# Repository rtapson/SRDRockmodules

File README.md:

# SRDRockmodules
A repository of information about SR&amp;D Rock Modules from the 1980's.

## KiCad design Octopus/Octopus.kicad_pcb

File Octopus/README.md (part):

# Octopus

A clone of the SR&D Octopus — a MIDI-controlled switcher — built around a **Teensy 4.1**. Unlike the audio-path loop switchers this generally gets compared to, this version drives **16 independent relay lines** on eight ¼" TRS jacks. Each jack's tip and ring are separate isolated contact closures to its sleeve, which is the standard dual-footswitch convention (e.g. channel on the tip, reverb on the ring). You patch them to amp channel/function jacks, other pedals' footswitch inputs, and so on. All 16 lines are recalled together as a single "preset" over MIDI, exactly like a footswitch controller flipping a bank on the original unit.

A separate **button panel** board (in `panel/`) puts 8 RGB-lit buttons on the front of the case, one per jack, to set and show each jack's lines by hand (see [Button panel](#button-panel)).

**Status:** firmware, and schematics plus fully routed 2-layer PCBs for both boards, are done. The hardware files are generated by scripts in `tools/` and verified with `kicad-cli` (ERC, DRC with schematic parity), full netlist checks, and rendered previews. Open `Octopus.kicad_pro` and `panel/OctopusPanel.kicad_pro` in KiCad to review. Both boards are fitted to the Rockmodule case model in `case/` (see [Fit in the case](#fit-in-the-case)). Nothing has been fabricated or bench-tested yet.

## Block diagram

```
MIDI IN (J1, FM6725) --220R--> 6N138 opto (isolated) --> Teensy 4.1 RX1 (3.3 V side)
                                                   \--> 74HCT14 x2 (5 V) --220R--> MIDI THRU (J12, FM6725)

                        +--------------------------+
                        |  Teensy 4.1              |
                        |  - MIDI parsing          |
                        |  - preset table (EEPROM) |
                        |  pins 2-9    pins 24-31  |
                        +--------------------------+
                               |            |
                               v            v
                        ULN2803A U3    ULN2803A U5      (sink the relay coils)
                               |            |
                               v            v
                     8x relay (tips)         8x relay (rings)
                               |            |
                  8x NO/NC jumper         8x NO/NC jumper
                               |            |
                               v            v
            8x Switchcraft RN112BPC 1/4" TRS jack: tip = line n, ring = line n+8, sleeve = common

9-12VDC in (J2 screw terminal) --> polyfuse --> Recom R-78E 5 V switcher --> +5V: Teensy VIN, relay coils, ULN COMs
Teensy 3.3 V pin --> +3V3: 6N138 output side + RX1 pull-up

Teensy I2C0 (pins 18/19) + pin 22 --J11, 6-pin cable--> button panel: 8x red/green button, PCA9685, MCP23017, OLED, encoder
```

## Bill of materials

`BOM_DigiKey.csv` lists every part for one unit (both boards and the panel cable) by manufacturer part number, ready to upload to DigiKey's BOM Manager. Mechanical hardware isn't in it: see the notes after the table below.

| Ref | Part | Footprint | Notes |
|---|---|---|---|
| U1 | PJRC Teensy 4.1 | `Octopus:Teensy41_Socketed` | Mounted on 2x24 female headers. Custom symbol/footprint in this folder (`Octopus.kicad_sym`, `Octopus.pretty`); only the pins this design uses are in the symbol |
| U2 | 6N138 | DIP-8 | MIDI IN opto-isolator; output side runs from the Teensy's 3.3 V |
| U3, U5 | ULN2803A | DIP-18 | Octal Darlington sink drivers (U3 = tip lines, U5 = ring lines), internal flyback diodes |
| U4 | Recom R-78E5.0-1.0 | SIP-3 (`RECOM_R-78E`) | 5 V / 1 A switching regulator, 7805 pinout. Runs cool at the ~630 mA load, where a 7805 would burn ~4.4 W from 12 V |
| C1 | 10 µF 25 V electrolytic | radial 6.3 mm | Regulator input capacitor |
| C2 | 22 µF 16 V electrolytic | radial 6.3 mm | Regulator output capacitor |
| K1-K16 | Omron G5V-1 (5 VDC coil) | `Relay_SPDT_Omron_G5V-1` | SPDT: COM = pins 5+6, NC = pin 1, NO = pin 10. K1-K8 switch jack tips, K9-K16 rings |
| D1 | 1N4148 | DO-35 | Reverse-parallel across the opto LED (MIDI reverse-voltage protection) |
| R1 | 220 Ω | axial 0207 | In series between DIN pin 4 and the opto LED (MIDI spec) |
| R2 | 470 Ω | axial 0207 | Opto output pull-up to **3.3 V** (Teensy 4.1 pins are not 5 V tolerant) |
| J1 | Cliff FM6725 (DIN-5 180°, screened, right-angle PCB) | `Octopus:DIN-5_180deg_Cliff_FM6725_Horizontal` | **MIDI IN**, through the back panel. Only pins 4 and 5 are used; pin 2 and the screen are left unconnected, as the MIDI spec requires for an input |
| J12 | Cliff FM6725 | `Octopus:DIN-5_180deg_Cliff_FM6725_Horizontal` | **MIDI THRU**, through the back panel. Pin 4 → 220 Ω → +5 V, pin 5 → 220 Ω → U6, pin 2 and the screen to GND |
| U6 | 74HCT14 | DIP-14 | MIDI THRU buffer: two inverters in series from the opto output. HCT's TTL input thresholds take the 3.3 V signal while it drives the 5 V MIDI loop. The other four gates' inputs are grounded |
| R3, R4 | 220 Ω | axial 0207 | MIDI THRU source resistors (pins 4 and 5) |
| C3 | 100 nF ceramic | disc, 5 mm pitch | U6 decoupling |
| J2 | 2-way 5.08 mm screw terminal (Phoenix MKDS 1,5/2-5.08) | TerminalBlock_Phoenix_MKDS-1,5-2-5.08 | 9-12 VDC in (1 = +, 2 = GND). The back panel has no DC jack hole, so this takes a pigtail through the cord hole now, and the DC output of a mains module later |
| J3-J10 | Switchcraft RN112BPC | `RN112BPC:SWITCHCRAFT_RN112BPC` (SnapMagic, in `case/RN112BPC`) | Outputs 1-8 (jack 1 is the leftmost seen from the back). ¼" 3-conductor right-angle Hi-D Jax, double open circuit, thermoplastic body, PC terminals. Tip = line n, ring = line n+8, sleeve = common for both |
| JP1-JP16 | 3-pad solder jumper (PCB copper, not a part) | `SolderJumper-3_P1.3mm_Bridged12` | Per-line NO/NC select, on the **bottom** side directly behind each relay, labelled NO / NC. Ships bridged to **NO**: the jack contact is shorted to sleeve while the line is on. For **NC** (open while the line is on), cut the thin trace between the "NO" pad and the center pad, then solder-bridge the center pad to the "NC" pad |
| F1 | Bourns MF-RHT070 (0.7 A hold) | radial | Input polyfuse |
| J11 | JST-XH 6-pin (B6B-XH-A) | JST_XH_B6B-XH-A | Cable to the button panel's J1, wired pin-for-pin: 1 +5V, 2 +3V3, 3 GND, 4 SDA, 5 SCL, 6 INT |
| H1, H2 | M3 mounting holes | 3.2 mm | On the case floor's two screw bosses; the jack nuts hold the back edge. Needs ~1.8-2 mm spacers (see below) |

## Pin map (Teensy 4.1)

| Teensy pin | Function |
|---|---|
| 0 (RX1) | MIDI IN (Serial1), from the opto output. The same node feeds the hardware MIDI THRU, so THRU works whatever the firmware is doing; the MIDI library's software thru is turned off |
| 2-9 | Lines 1-8 (jack 1-8 **tip**) via U3 |
| 24-31 | Lines 9-16 (jack 1-8 **ring**) via U5 |
| 18, 19 | I2C0 SDA / SCL to the button panel (pull-ups are on the panel) |
| 22 | Button panel interrupt (MCP23017 INTA, open-drain, Teensy internal pull-up) |
| VIN | +5 V from U4 |
| 3.3V | Powers the 6N138 output side and the RX1 pull-up |
| GND | Common ground |
| USB | Config/debug console (see `firmware/README.md`) |

The firmware's pin table (`firmware/src/RelayBank.cpp`) uses this same map. Pins 2-9 and 24-31 are the two runs of consecutive pins along one header row, so each driver sits directly under its group. Within each driver, slot *k* uses input I(9−k)/output O(9−k). That reversal only exists so the driver traces run straight, and it's invisible to the firmware.

## MIDI control spec

- **Program Change (0-127)** recalls stored preset 1-128 (PC 0 = preset 1, as shown on the display): all 16 lines are set at once from that preset's 16-bit pattern (bit N = line N+1, 1 = on).
- **Control Change 102-117** switches line 1-16 individually: value >= 64 = on, < 64 = off. These CCs are left undefined by the MIDI spec. The old 8-line range (20-27) couldn't simply be extended to 20-35, because CC 32 is Bank Select LSB.
- **MIDI channel**: omni by default; can be pinned to a single channel via the serial config console (see firmware README).
- Presets and channel persist across power cycles in the Teensy's emulated EEPROM.

## PCB

- One flat, 2-layer board, 205.8 × 111.7 mm, all through-hole except the 16 solder jumpers (bare copper on the bottom). GND pour on both layers.
- Layout, from the back edge forward: the eight RN112BPC jacks on a 17.78 mm (0.700") pitch, then the MIDI IN and THRU sockets and the power terminal J2 just inside the cord hole; for each jack, its tip relay and ring relay side by side; the two ULN2803As, each directly behind its Teensy pin group; the Teensy (USB toward the right side). The MIDI opto, THRU buffer and regulator are just in front of the DIN sockets. The button-panel header J11 is at the front edge.
- Net classes (in `Octopus.kicad_pro`): Default 0.3 mm, **Power** (+5V, GND, raw DC in) 0.8 mm, **Relay** (the `/CHn_*` and `/JACKn_SLV` contact nets) 0.6 mm, which is ample for the relays' 1 A rating. Relay clearance is 0.24 mm because the solder jumper's pads are 0.25 mm apart by design, which is fine for the low-voltage duty these relays are limited to anyway (see cautions). Freerouting routes with a 10 µm margin over every clearance, so its rounding can't land a track under KiCad's rule.
- Verified: `kicad-cli pcb drc --schematic-parity --refill-zones` → 0 errors, 0 unconnected, 0 parity issues; ERC 0 errors. The only DRC warnings are 16 × *silkscreen clipped by board edge*: SnapMagic's RN112BPC outline includes the bushing, which overhangs the back edge by design. The library footprint is used exactly as supplied, so these are left alone.
- Jack 8's tip run (from its tip pin, down the gap beside the rear-post notch, to JP8 under relay K8) is laid by hand and locked before autorouting (`add_preroutes()` in `gen_pcb.py`); Freerouting otherwise boxes that pin in.

### Fit in the case

Measured from `case/Bottom.step`, `Top.step` and `BackPanel.step` (the back panel's STEP sits 53.34 mm behind the case; it belongs in the back groove, inside face at y = 64.77 mm in the case frame). All in `tools/gen_pcb.py`, `case geometry` section.

- **Jacks.** The RN112BPC is a right-angle jack: it lies on the board, pins down, with its plug axis 9.65 mm (0.380") above the board surface. Its body's front face seats against the inside of the back panel and the 3/8-32 bushing passes through the Ø9.52 mm hole; the washer and nut go on the outside and hold the board's back edge. The symbol, footprint and 3D model are SnapMagic's (`case/RN112BPC`, wired in through the project's `sym-lib-table` and `fp-lib-table`). The footprint agrees with Switchcraft's customer drawing *RN111-RN114 SERIES, right angle Hi-D Jax* rev E: its origin is the sleeve pin, 5.68 mm behind the body's front face, and the tip pin is 12.70 mm further back. The locating-post holes are 2.69 mm, against the drawing's 2.41 mm. The schematic generator embeds the symbol after upgrading it with `kicad-cli sym upgrade` (it's in KiCad 6 format). `gen_pcb.py` attaches the STEP model when it places the jacks, turned 180° and shifted 12.7 mm to match the footprint. The model also contains the nut and washer, drawn floating in front of the bushing, and a flat 'confidential' label plate; both are cosmetic and only show in the 3D view.
- **Board height.** The jack holes are 18.10 mm above the case bottom, so the board's top must sit at **8.45 mm**, bottom at 6.85 mm. The floor bosses' tops are at 5.02 mm (right one 4.89 mm), so put **~1.8-2.0 mm spacers** (nylon washers, or 2 mm M3 spacers) between the bosses and the board. The panel holes are the same size as the bushings, so the jacks can't take up much error: check the height with the jacks' nuts loose before tightening.
- **DIN sockets.** The FM6725 is a right-angle socket with its front face on the inside of the panel, like the jacks, so its centre is 10.3 mm above the board: **18.75 mm** above the case bottom, 0.65 mm higher than the jacks. The footprint follows the Cliff datasheet (`case/screeneddins.pdf`) and was checked against `case/FM6725.stp`, which KiCad uses as the 3D model. That model puts the centre 0.2 mm lower, at 10.1 mm, which a Ø15 panel hole easily absorbs.
- **Outline.** It fills the case between the side walls (x ±102.9 mm), from 64.2 mm (0.57 mm short of the back panel; the bushings overhang the edge) to 47.5 mm forward of centre, which clears the parts on the back of the button board. The three screw posts that join the case halves (4.75 mm radius at board height) pass through a Ø10.5 mm hole at the front and two notches at the back corners. The jack bodies end about 2 mm in front of the rear posts. Jack 8's two relays sit further forward, below the notch, because the left rear post is where they would go.
- **Headroom.** The case roof is 32.6 mm above the board, which clears everything (the Teensy on headers is ~13 mm, the jacks 17 mm). Under the board, 4.6 mm clears the trimmed through-hole leads.
- **Future mains power.** The DIN sockets now fill the back corner, so the space kept free for a 12 V mains module is the **front right** of the board (~50 × 52 mm, marked on `Dwgs.User`), with the cord running forward to it from the hole. Its DC output goes to J2, so the regulator stays as it is.

### Back panel holes

The main board fixes where every hole in the back panel goes. Jack 8 sits 0.8 mm clear of the left groove rib, and from jack 1 on come MIDI IN, MIDI THRU and the cord hole, 1.5 mm apart. **These differ from the current `BackPanel.step`:** the jacks close up from a 0.75" to a 0.700" pitch, the two DIN holes are new, and the cord hole moves 3.67 mm toward the edge. Positions are measured on the panel **seen from behind the unit**, from its left and bottom edges (the panel is 211.18 × 38.61 mm). The last three columns are the same centres in the case frame of the STEP files (x across, z up), plus how far each hole moved.

| Hole | From left edge (mm) | From bottom edge (mm) | Diameter (mm) | Case x | Case z | Moved in x |
|---|---|---|---|---|---|---|
| Power cord | 13.79 | 19.31 | 14.48 | 91.68 | 21.53 | +3.67 |
| MIDI THRU | 33.03 | 16.53 | 15.0 | 72.44 | 18.75 | new |
| MIDI IN | 55.53 | 16.53 | 15.0 | 49.94 | 18.75 | new |
| Jack 1 | 75.47 | 15.88 | 9.52 | 30.00 | 18.10 | −10.34 |
| Jack 2 | 93.25 | 15.88 | 9.52 | 12.22 | 18.10 | −9.07 |
| Jack 3 | 111.03 | 15.88 | 9.52 | −5.56 | 18.10 | −7.80 |
| Jack 4 | 128.81 | 15.88 | 9.52 | −23.34 | 18.10 | −6.53 |
| Jack 5 | 146.59 | 15.88 | 9.52 | −41.12 | 18.10 | −5.26 |
| Jack 6 | 164.37 | 15.88 | 9.52 | −58.90 | 18.10 | −3.99 |
| Jack 7 | 182.15 | 15.88 | 9.52 | −76.68 | 18.10 | −2.72 |
| Jack 8 | 199.93 | 15.88 | 9.52 | −94.46 | 18.10 | −1.45 |

The DIN holes only need to pass the plug's shell into the socket (Ø14 opening), so Ø15.0 is a suggestion; check it against your cables. The 0.700" pitch leaves ~1.9 mm between the 15.88 mm jack bodies, and between the washers (0.625" max per Switchcraft).

### Cautions before ordering

1. **Power.** Worst-case 5 V load is about 800 mA: 16 coils × 30 mA, the Teensy, and all 8 buttons lit amber (≈26 mA each: 10 mA red + 16 mA green). That's within the R-78E5.0-1.0's 1 A. From 12 V it draws about 0.4 A at the input, comfortably under the polyfuse's 0.7 A hold. The panel's logic (~10 mA) runs from the Teensy's 3.3 V pin, which can supply 250 mA.
2. **Teensy VIN/VUSB.** If USB may be plugged in while J2 is powered, cut the VIN–VUSB trace on the Teensy's underside (per PJRC). Otherwise the two supplies back-feed each other.
3. **Contact ratings.** The G5V-1 is rated 1 A at 30 VDC (0.5 A at 125 VAC), and the board's clearances are sized for low voltage. **Don't switch mains** with this board as-is. Likewise, don't bring the mains cord onto this board: a mains module needs its own creepage-rated wiring and fusing.
4. **Shared sleeve.** A jack's tip and ring lines share its sleeve as their common, as dual footswitches expect. They are not isolated from each other the way separate jacks are.
5. **No status LEDs on the main board.** The front-panel buttons show every line. For bench testing without the button board, the serial console (`DUMP`) or a meter on the jacks will show what's switched.

## Button panel

A separate board (`panel/OctopusPanel.*`) slides into the groove in the case top and bottom, just behind the front panel, with 8 illuminated buttons (one per output jack), a 0.96" OLED showing the current preset, and a rotary encoder with push switch for picking presets.

| Button LED | Jack state |
|---|---|
| off | tip and ring both off |
| red | tip on |
| green | ring on |
| amber (red + green) | tip and ring both on |

- **Press** (acts on release) to step a jack: off → red → green → amber → off.
- **Hold 2 s** to save all 16 lines into the current preset (the one on the display). The LEDs blink off once, the display says SAVED, and the serial console prints the number.
- **Display:** the current preset, **1-128** (MIDI Program Change 0 = preset 1), in big digits. "EDITED" appears when the buttons have changed the lines since the preset was loaded (hold a button to save it, or recall the preset to drop the change).
- **Encoder:** turn to pick a preset. The display shows it under an inverted SELECT? label (turning wraps 128 → 1). **Push** to load it, which is the same as a MIDI Program Change. Leave it for 5 s and the display goes back to the current preset without changing anything.
- The LEDs always mirror the relays, so MIDI program changes and CCs show up on the buttons too.
- If the panel isn't connected, the main board runs normally without it.

**Circuit.** The switches are **Omron B3W-9000-RG2N**: 10 × 10 mm milky-white cap, with a red and a green LED on separate leads. Both anodes go to +5V, and each cathode has its own resistor: 330 Ω red (≈10 mA) and 180 Ω green (≈16 mA), in four isolated 4-resistor arrays (Bourns CAT16-331J4 / -181J4, 1206). RN1 and RN2 carry the red of buttons 1-4 and 5-8, RN3 and RN4 the green. Each element dissipates at most ~46 mW of its 62.5 mW rating. That's Omron's recommended 12:20 red:green ratio for an even amber, scaled down a little. The cathodes go to one **PCA9685** PWM LED driver (U1 @0x40: red LED0-7, green LED8-15). The chip runs at 3.3 V with open-drain outputs, which are 5.5 V tolerant, so the Teensy's I²C stays at 3.3 V (NXP datasheet, "direct LED connection"). The buttons and the encoder go to an **MCP23017** (U3 @0x20: buttons 1-7 on GPA0-6, button 8 on GPB0, encoder A/B/push on GPB1-3), with its interrupt (INTA, mirrored for both ports) on Teensy pin 22. GPA7 and GPB7 are left unused: Microchip's current datasheet makes them output-only. Each encoder line has a 10 kΩ pull-up and 10 nF to ground. The display is a **Winstar WEA012864D-03** 0.96" 128×64 SSD1306 module at I²C 0x3C, powered from 3.3 V (12 mA typical). Generic 0.96" modules usually share its outline, but check the pin order: many swap VCC and GND, and this board expects VCC, GND, SCL, SDA from the left, seen from the front. The only I²C pull-ups (4.7 kΩ) are on the panel. Red and green brightness (and so the amber mix) can be trimmed in firmware (`kLevelRed/Green` in `Panel.h`).

*Why not RGB?* The first choice, CTS 228CMVARGBFR, is discontinued, and no stocked RGB tactile switch was tall enough to reach through the panel. The only RGB one found, E-Switch TL3220, is 2 mm tall and would need custom light-pipe caps. With two LEDs, "both lines on" shows as amber, the mix of the other two colours.

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
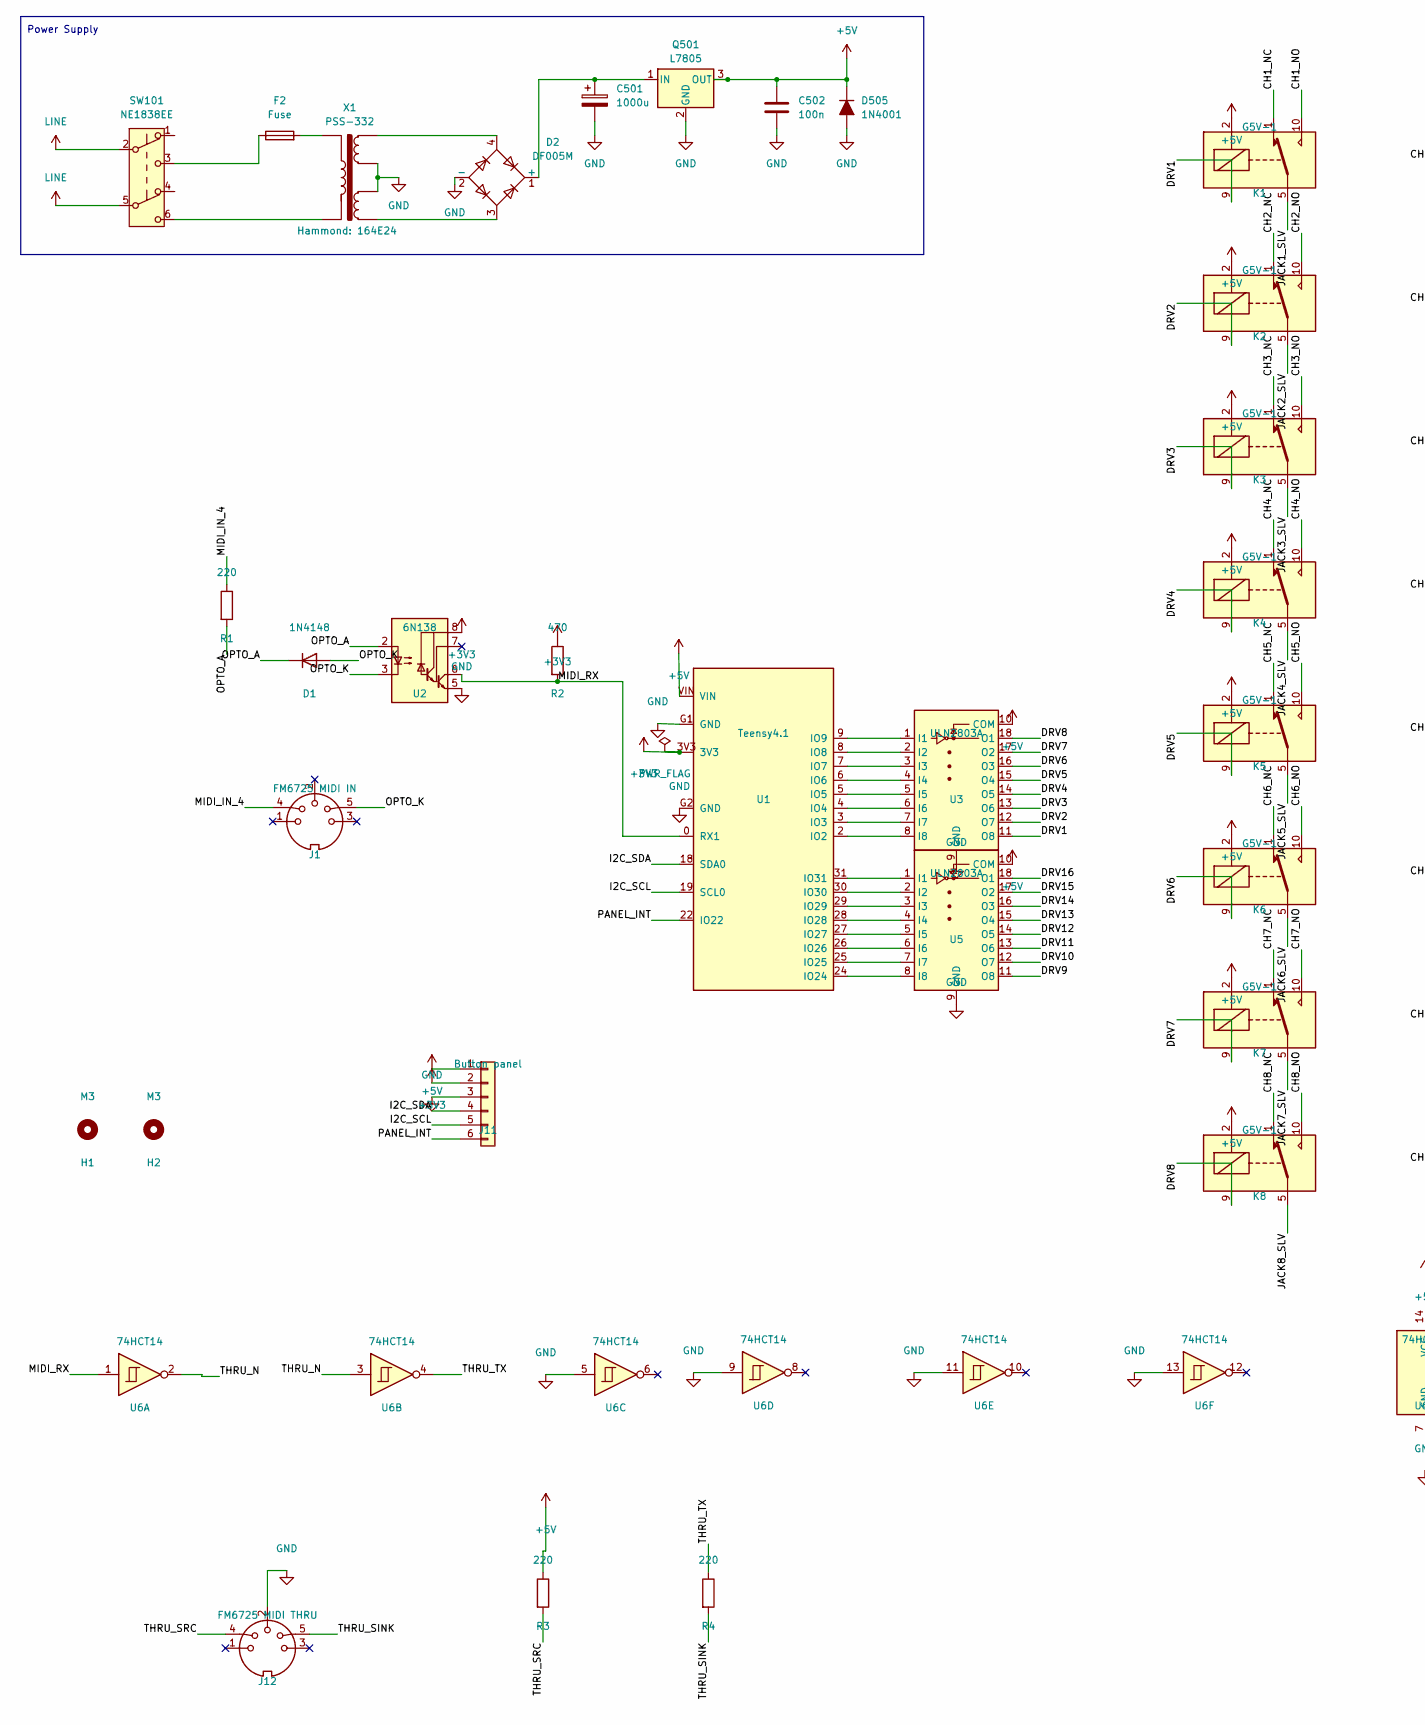
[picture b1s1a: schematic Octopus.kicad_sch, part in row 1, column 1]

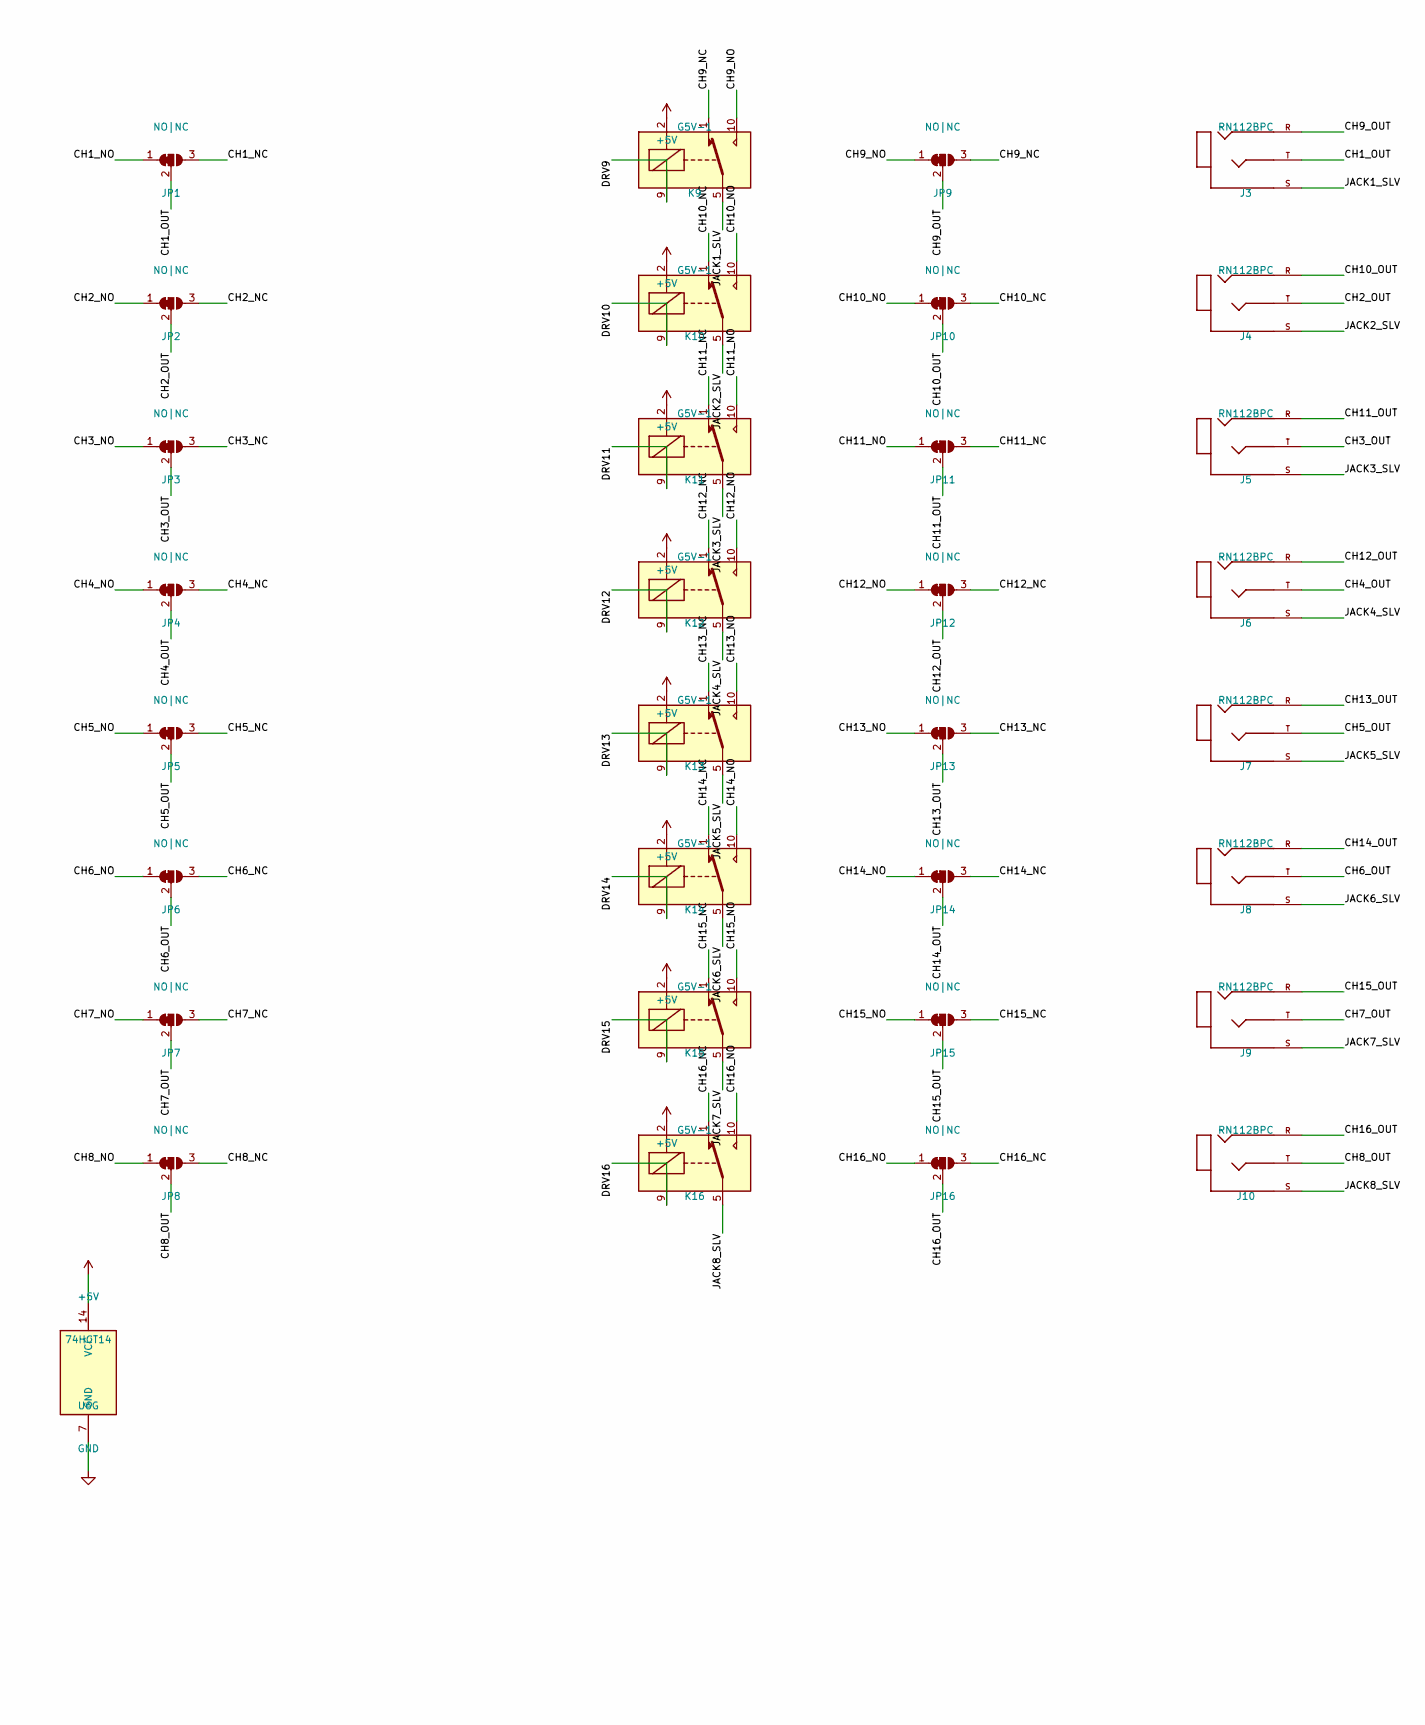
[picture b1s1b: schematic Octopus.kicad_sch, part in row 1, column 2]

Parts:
C501: 1000u; CP_Radial_D10.0mm_P5.00mm
C502: 100n; C_Disc_D10.0mm_W2.5mm_P5.00mm
D1: 1N4148; D_DO-35_SOD27_P7.62mm_Horizontal
D2: DF005M; Diode_Bridge_DIP-4_W7.62mm_P5.08mm
D505: 1N4001; D_A-405_P12.70mm_Horizontal
F2: Fuse; Fuseholder_Littelfuse_100_series_5x30mm
H1, H2: M3; MountingHole_3.2mm_M3
J1: FM6725 MIDI IN; DIN-5_180deg_Cliff_FM6725_Horizontal
J3, J4, J5, J6, J7, J8, J9, J10: RN112BPC; SWITCHCRAFT_RN112BPC
J11: Button panel; JST_XH_B6B-XH-A_1x06_P2.50mm_Vertical
J12: FM6725 MIDI THRU; DIN-5_180deg_Cliff_FM6725_Horizontal
JP1, JP2, JP3, JP4, JP5, JP6, JP7, JP8, JP9, JP10, JP11, JP12, JP13, JP14, JP15, JP16: NO|NC; SolderJumper-3_P1.3mm_Bridged12_RoundedPad1.0x1.5mm
K1, K2, K3, K4, K5, K6, K7, K8, K9, K10, K11, K12, K13, K14, K15, K16: G5V-1; Relay_SPDT_Omron_G5V-1
Q501: L7805; TO-220-3_Vertical
R1, R3, R4: 220; R_Axial_DIN0207_L6.3mm_D2.5mm_P10.16mm_Horizontal
R2: 470; R_Axial_DIN0207_L6.3mm_D2.5mm_P10.16mm_Horizontal
SW101: NE1838EE; NE18_2U_EE_P_6AMP
U1: Teensy4.1; Teensy41_Socketed
U2: 6N138; DIP-8_W7.62mm
U3, U5: ULN2803A; DIP-18_W7.62mm
U6: 74HCT14; DIP-14_W7.62mm
X1: PSS-332; Transformer_Hammond_164D_1.1VA

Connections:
+3V3: J11.2, R2.1, U1.3V3, U2.8 (VCC)
+5V: C502.1, D505.1 (K), J11.1, K1.2, K2.2, K3.2, K4.2, K5.2, K6.2, K7.2, K8.2, K9.2, K10.2, K11.2, K12.2, K13.2, K14.2, K15.2, K16.2, Q501.3 (OUT), R3.1, U1.VIN, U3.10 (COM), U5.10 (COM), U6.14 (VCC); also elsewhere on the board
/CH1_NC: JP1.3 (B), K1.1
/CH1_NO: JP1.1 (A), K1.10
/CH1_OUT: J3.T, JP1.2 (C)
/CH2_NC: JP2.3 (B), K2.1
/CH2_NO: JP2.1 (A), K2.10
/CH2_OUT: J4.T, JP2.2 (C)
/CH3_NC: JP3.3 (B), K3.1
/CH3_NO: JP3.1 (A), K3.10
/CH3_OUT: J5.T, JP3.2 (C)
/CH4_NC: JP4.3 (B), K4.1
/CH4_NO: JP4.1 (A), K4.10
/CH4_OUT: J6.T, JP4.2 (C)
/CH5_NC: JP5.3 (B), K5.1
/CH5_NO: JP5.1 (A), K5.10
/CH5_OUT: J7.T, JP5.2 (C)
/CH6_NC: JP6.3 (B), K6.1
/CH6_NO: JP6.1 (A), K6.10
/CH6_OUT: J8.T, JP6.2 (C)
/CH7_NC: JP7.3 (B), K7.1
/CH7_NO: JP7.1 (A), K7.10
/CH7_OUT: J9.T, JP7.2 (C)
/CH8_NC: JP8.3 (B), K8.1
/CH8_NO: JP8.1 (A), K8.10
/CH8_OUT: J10.T, JP8.2 (C)
/CH9_NC: JP9.3 (B), K9.1
/CH9_NO: JP9.1 (A), K9.10
/CH9_OUT: J3.R, JP9.2 (C)
/CH10_NC: JP10.3 (B), K10.1
/CH10_NO: JP10.1 (A), K10.10
/CH10_OUT: J4.R, JP10.2 (C)
/CH11_NC: JP11.3 (B), K11.1
/CH11_NO: JP11.1 (A), K11.10
/CH11_OUT: J5.R, JP11.2 (C)
/CH12_NC: JP12.3 (B), K12.1
/CH12_NO: JP12.1 (A), K12.10
/CH12_OUT: J6.R, JP12.2 (C)
/CH13_NC: JP13.3 (B), K13.1
/CH13_NO: JP13.1 (A), K13.10
/CH13_OUT: J7.R, JP13.2 (C)
/CH14_NC: JP14.3 (B), K14.1
/CH14_NO: JP14.1 (A), K14.10
/CH14_OUT: J8.R, JP14.2 (C)
/CH15_NC: JP15.3 (B), K15.1
/CH15_NO: JP15.1 (A), K15.10
/CH15_OUT: J9.R, JP15.2 (C)
/CH16_NC: JP16.3 (B), K16.1
/CH16_NO: JP16.1 (A), K16.10
/CH16_OUT: J10.R, JP16.2 (C)
/DRV1: K1.9, U3.11 (O8)
/DRV2: K2.9, U3.12 (O7)
/DRV3: K3.9, U3.13 (O6)
/DRV4: K4.9, U3.14 (O5)
/DRV5: K5.9, U3.15 (O4)
/DRV6: K6.9, U3.16 (O3)
/DRV7: K7.9, U3.17 (O2)
/DRV8: K8.9, U3.18 (O1)
/DRV9: K9.9, U5.11 (O8)
/DRV10: K10.9, U5.12 (O7)
/DRV11: K11.9, U5.13 (O6)
/DRV12: K12.9, U5.14 (O5)
/DRV13: K13.9, U5.15 (O4)
/DRV14: K14.9, U5.16 (O3)
/DRV15: K15.9, U5.17 (O2)
/DRV16: K16.9, U5.18 (O1)
/I2C_SCL: J11.5, U1.19 (SCL0)
/I2C_SDA: J11.4, U1.18 (SDA0)
/JACK1_SLV: J3.S, K1.5, K1.6, K9.5, K9.6
/JACK2_SLV: J4.S, K2.5, K2.6, K10.5, K10.6
/JACK3_SLV: J5.S, K3.5, K3.6, K11.5, K11.6
/JACK4_SLV: J6.S, K4.5, K4.6, K12.5, K12.6
/JACK5_SLV: J7.S, K5.5, K5.6, K13.5, K13.6
/JACK6_SLV: J8.S, K6.5, K6.6, K14.5, K14.6
/JACK7_SLV: J9.S, K7.5, K7.6, K15.5, K15.6
/JACK8_SLV: J10.S, K8.5, K8.6, K16.5, K16.6
/MIDI_IN_4: J1.4, R1.1
/MIDI_RX: R2.2, U1.0 (RX1), U2.6 (VO2), U6.1; also elsewhere on the board
/OPTO_A: D1.1 (K), R1.2, U2.2 (C1)
/OPTO_K: D1.2 (A), J1.5, U2.3 (C2)
/PANEL_INT: J11.6, U1.22 (IO22)
/THRU_N: U6.2, U6.3; also elsewhere on the board
/THRU_SINK: J12.5, R4.2
/THRU_SRC: J12.4, R3.2
/THRU_TX: R4.1, U6.4; also elsewhere on the board
GND: C501.2, C502.2, D2.2 (-), D505.2 (A), J11.3, J12.2, Q501.2 (GND), U1.G1 (GND), U1.G2 (GND), U2.5 (GND), U3.9 (GND), U5.9 (GND), U6.5, U6.7 (GND), U6.9, U6.11, U6.13, X1.4, X1.5; also elsewhere on the board
LINE: SW101.2 (B), SW101.5 (B)
unnamed: C501.1, D2.1 (+), Q501.1 (IN)
unnamed: D2.3, X1.6
unnamed: D2.4, X1.3
unnamed: F2.1, SW101.3 (C)
unnamed: F2.2, X1.1
unnamed: SW101.6 (C), X1.2
unnamed: U1.2 (IO2), U3.8 (I8)
unnamed: U1.3 (IO3), U3.7 (I7)
unnamed: U1.4 (IO4), U3.6 (I6)
unnamed: U1.5 (IO5), U3.5 (I5)
unnamed: U1.6 (IO6), U3.4 (I4)
unnamed: U1.7 (IO7), U3.3 (I3)
unnamed: U1.8 (IO8), U3.2 (I2)
unnamed: U1.9 (IO9), U3.1 (I1)
unnamed: U1.24 (IO24), U5.8 (I8)
unnamed: U1.25 (IO25), U5.7 (I7)
unnamed: U1.26 (IO26), U5.6 (I6)
unnamed: U1.27 (IO27), U5.5 (I5)
unnamed: U1.28 (IO28), U5.4 (I4)
unnamed: U1.29 (IO29), U5.3 (I3)
unnamed: U1.30 (IO30), U5.2 (I2)
unnamed: U1.31 (IO31), U5.1 (I1)

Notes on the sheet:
Power Supply

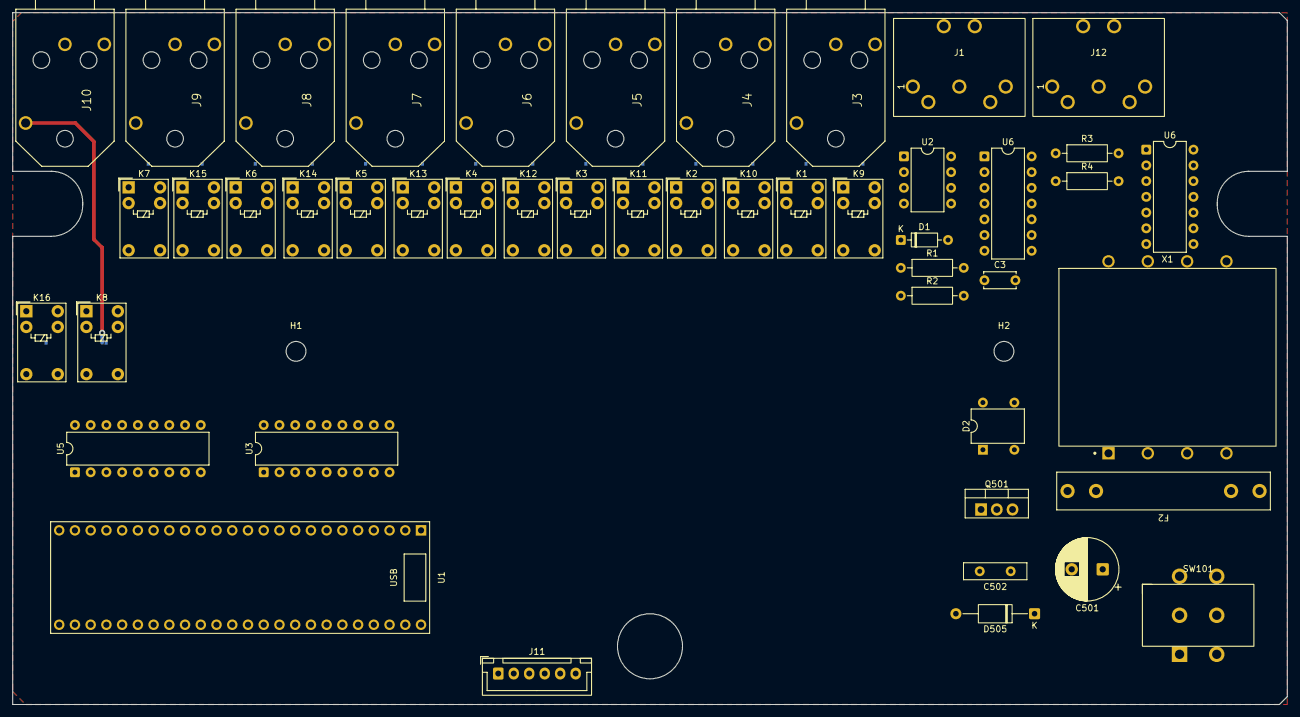
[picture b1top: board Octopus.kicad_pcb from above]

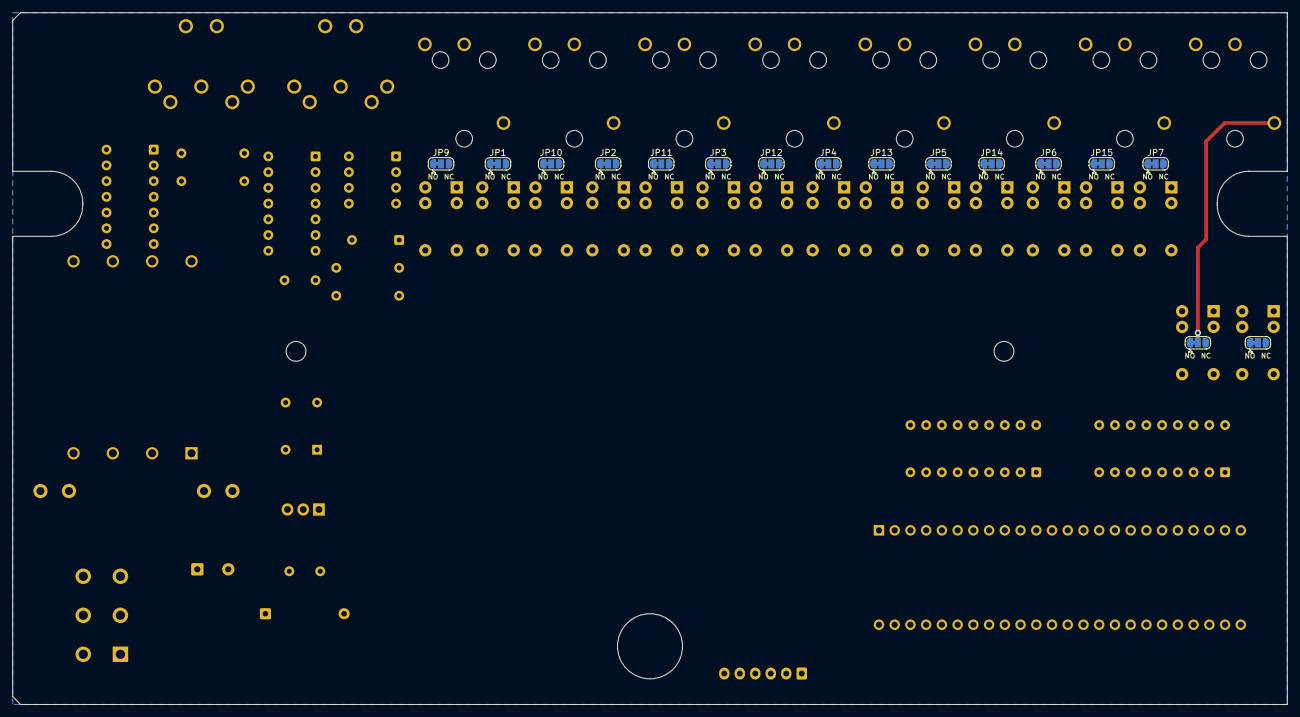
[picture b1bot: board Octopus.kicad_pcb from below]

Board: 2 copper layers, 205.8 x 111.7 mm, 65 parts (16 on the bottom side), 109 nets.

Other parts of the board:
C3: 100n; C_Disc_D5.0mm_W2.5mm_P5.00mm
U6#2: 74HCT14; DIP-14_W7.62mm

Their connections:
+5V: C3.1, U6#2.14 (VCC); also elsewhere on the board
/MIDI_RX: U6#2.1; also elsewhere on the board
/THRU_N: U6#2.2, U6#2.3; also elsewhere on the board
/THRU_TX: U6#2.4; also elsewhere on the board
GND: C3.2, U6#2.5, U6#2.7 (GND), U6#2.9, U6#2.11, U6#2.13; also elsewhere on the board

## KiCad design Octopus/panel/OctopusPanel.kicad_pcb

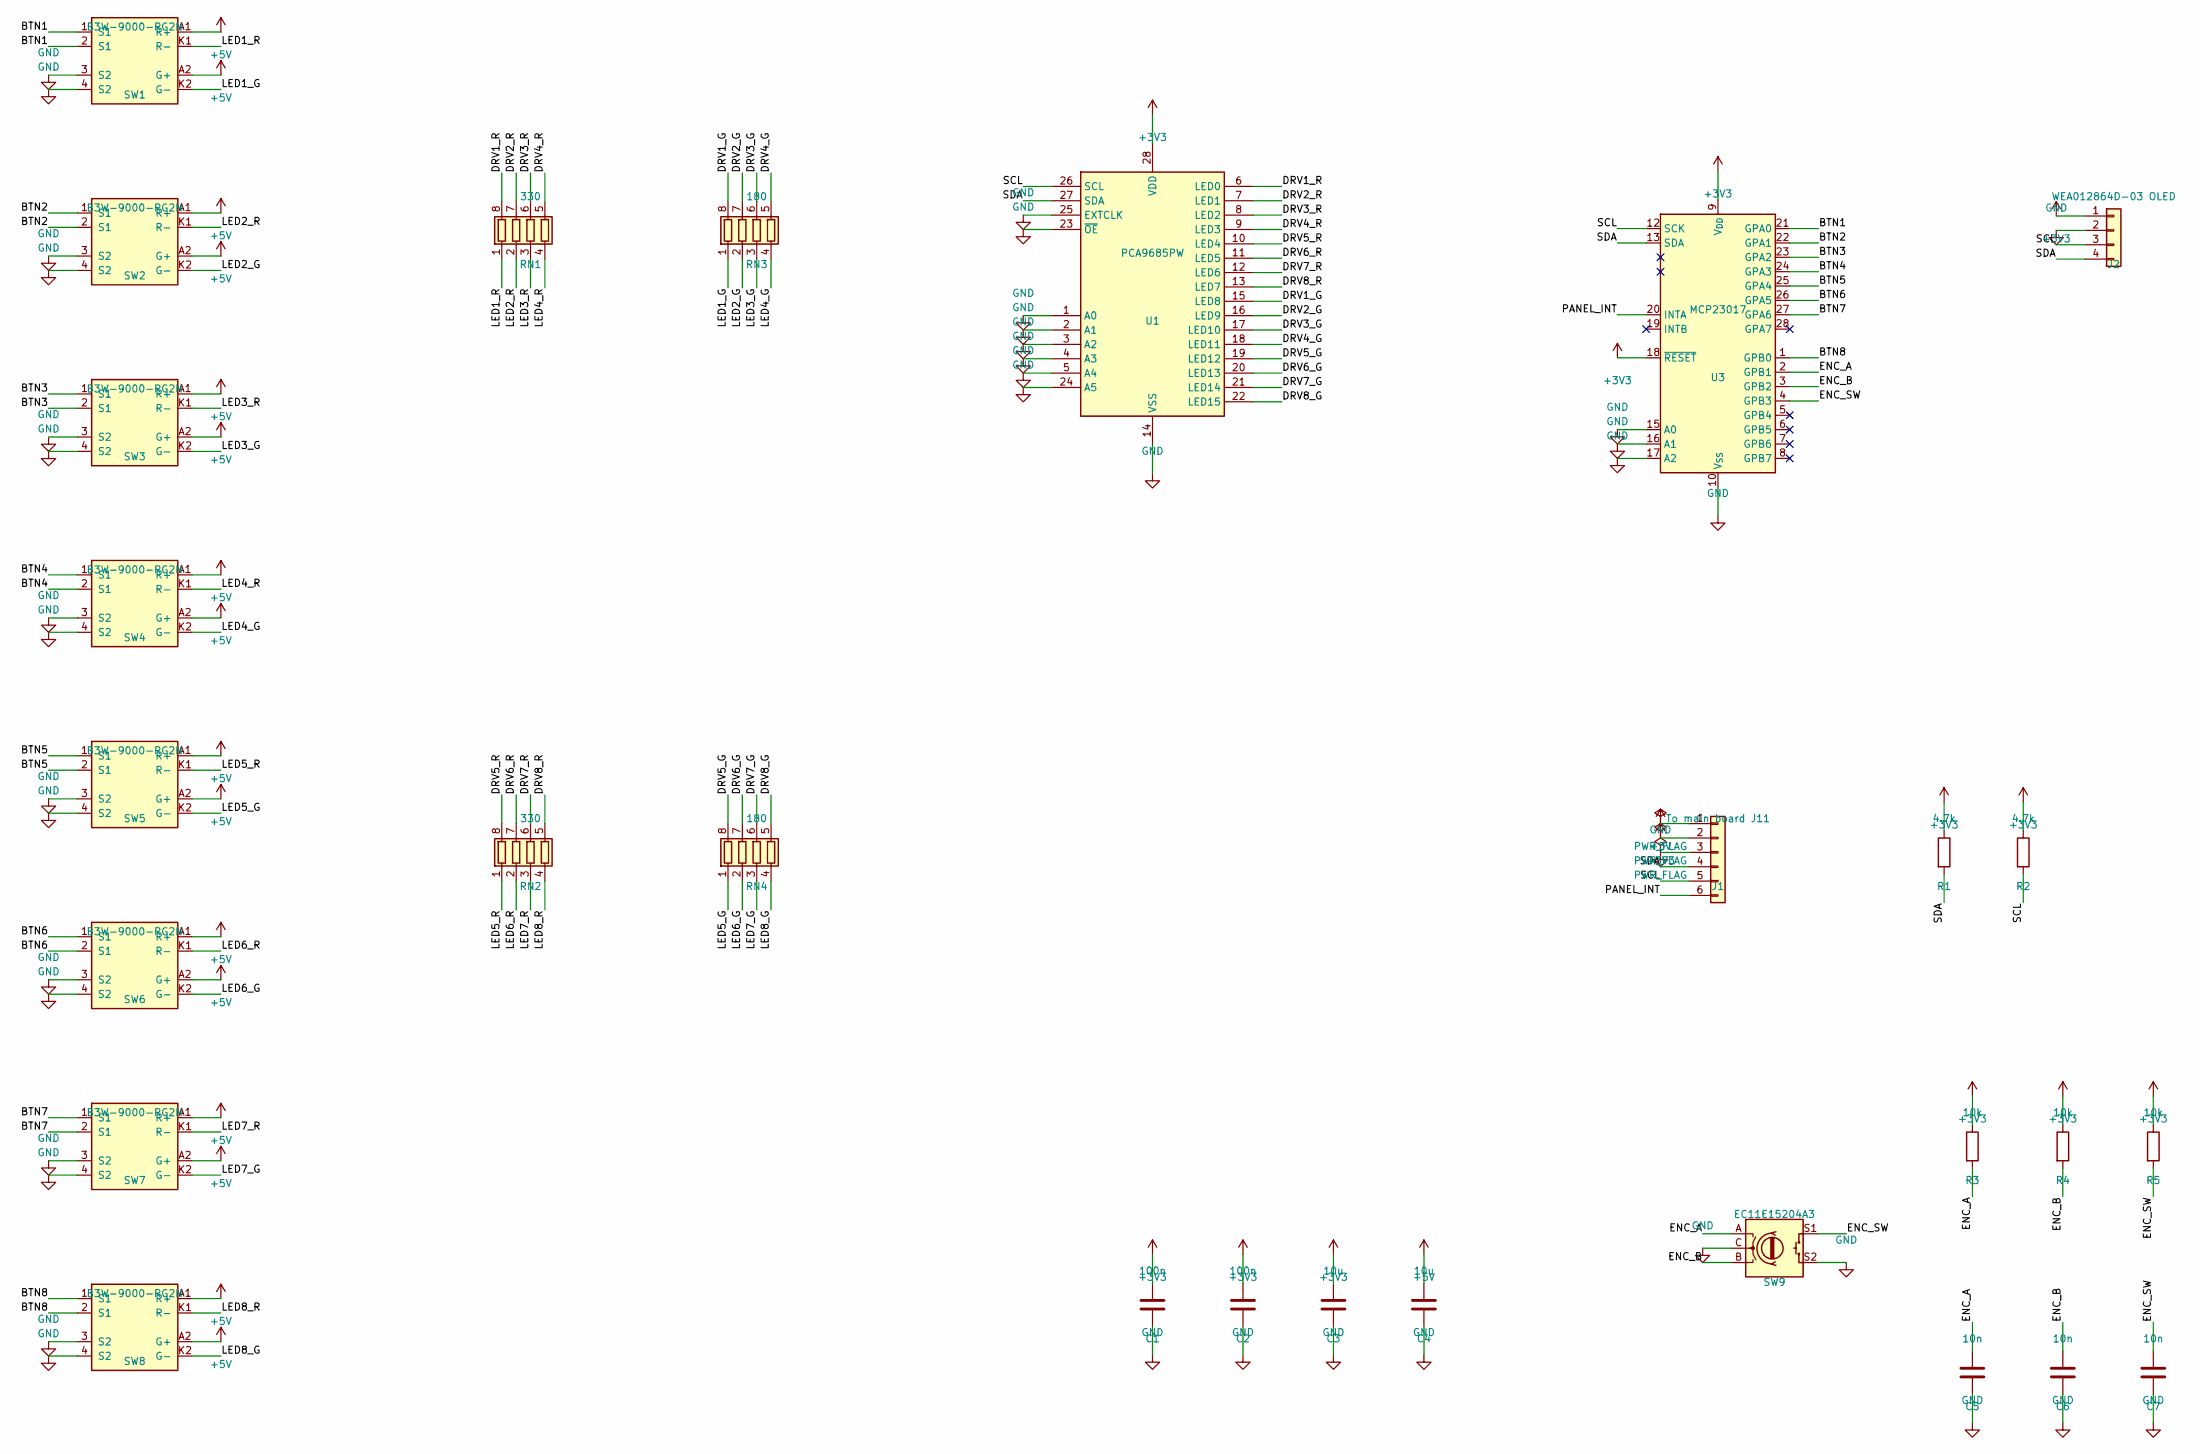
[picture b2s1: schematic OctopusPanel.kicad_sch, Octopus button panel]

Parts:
C1, C2: 100n; C_0805_2012Metric
C3, C4: 10u; C_0805_2012Metric
C5, C6, C7: 10n; C_0805_2012Metric
J1: To main board J11; JST_XH_B6B-XH-A_1x06_P2.50mm_Vertical
J2: WEA012864D-03 OLED; OLED_Winstar_WEA012864D-03
R1, R2: 4.7k; R_0805_2012Metric
R3, R4, R5: 10k; R_0805_2012Metric
RN1, RN2: 330; R_Array_Convex_4x0603
RN3, RN4: 180; R_Array_Convex_4x0603
SW1, SW2, SW3, SW4, SW5, SW6, SW7, SW8: B3W-9000-RG2N; Omron_B3W-9_2LED_10x10
SW9: EC11E15204A3; RotaryEncoder_Alps_EC11E-Switch_Vertical_H20mm
U1: PCA9685PW; TSSOP-28_4.4x9.7mm_P0.65mm
U3: MCP23017; SOIC-28W_7.5x17.9mm_P1.27mm

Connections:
/BTN1: SW1.1 (S1), SW1.2 (S1), U3.21 (GPA0)
/BTN2: SW2.1 (S1), SW2.2 (S1), U3.22 (GPA1)
/BTN3: SW3.1 (S1), SW3.2 (S1), U3.23 (GPA2)
/BTN4: SW4.1 (S1), SW4.2 (S1), U3.24 (GPA3)
/BTN5: SW5.1 (S1), SW5.2 (S1), U3.25 (GPA4)
/BTN6: SW6.1 (S1), SW6.2 (S1), U3.26 (GPA5)
/BTN7: SW7.1 (S1), SW7.2 (S1), U3.27 (GPA6)
/BTN8: SW8.1 (S1), SW8.2 (S1), U3.1 (GPB0)
/DRV1_G: RN3.8 (R1.2), U1.15 (LED8)
/DRV1_R: RN1.8 (R1.2), U1.6 (LED0)
/DRV2_G: RN3.7 (R2.2), U1.16 (LED9)
/DRV2_R: RN1.7 (R2.2), U1.7 (LED1)
/DRV3_G: RN3.6 (R3.2), U1.17 (LED10)
/DRV3_R: RN1.6 (R3.2), U1.8 (LED2)
/DRV4_G: RN3.5 (R4.2), U1.18 (LED11)
/DRV4_R: RN1.5 (R4.2), U1.9 (LED3)
/DRV5_G: RN4.8 (R1.2), U1.19 (LED12)
/DRV5_R: RN2.8 (R1.2), U1.10 (LED4)
/DRV6_G: RN4.7 (R2.2), U1.20 (LED13)
/DRV6_R: RN2.7 (R2.2), U1.11 (LED5)
/DRV7_G: RN4.6 (R3.2), U1.21 (LED14)
/DRV7_R: RN2.6 (R3.2), U1.12 (LED6)
/DRV8_G: RN4.5 (R4.2), U1.22 (LED15)
/DRV8_R: RN2.5 (R4.2), U1.13 (LED7)
/ENC_A: C5.1, R3.2, SW9.A, U3.2 (GPB1)
/ENC_B: C6.1, R4.2, SW9.B, U3.3 (GPB2)
/ENC_SW: C7.1, R5.2, SW9.S1, U3.4 (GPB3)
/LED1_G: RN3.1 (R1.1), SW1.K2 (G-)
/LED1_R: RN1.1 (R1.1), SW1.K1 (R-)
/LED2_G: RN3.2 (R2.1), SW2.K2 (G-)
/LED2_R: RN1.2 (R2.1), SW2.K1 (R-)
/LED3_G: RN3.3 (R3.1), SW3.K2 (G-)
/LED3_R: RN1.3 (R3.1), SW3.K1 (R-)
/LED4_G: RN3.4 (R4.1), SW4.K2 (G-)
/LED4_R: RN1.4 (R4.1), SW4.K1 (R-)
/LED5_G: RN4.1 (R1.1), SW5.K2 (G-)
/LED5_R: RN2.1 (R1.1), SW5.K1 (R-)
/LED6_G: RN4.2 (R2.1), SW6.K2 (G-)
/LED6_R: RN2.2 (R2.1), SW6.K1 (R-)
/LED7_G: RN4.3 (R3.1), SW7.K2 (G-)
/LED7_R: RN2.3 (R3.1), SW7.K1 (R-)
/LED8_G: RN4.4 (R4.1), SW8.K2 (G-)
/LED8_R: RN2.4 (R4.1), SW8.K1 (R-)
/PANEL_INT: J1.6, U3.20 (INTA)
/SCL: J1.5, J2.3, R2.2, U1.26 (SCL), U3.12 (SCK)
/SDA: J1.4, J2.4, R1.2, U1.27 (SDA), U3.13 (SDA)

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
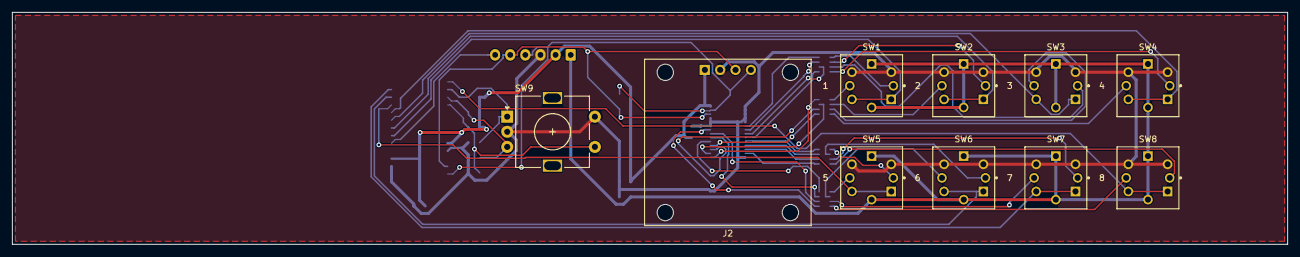
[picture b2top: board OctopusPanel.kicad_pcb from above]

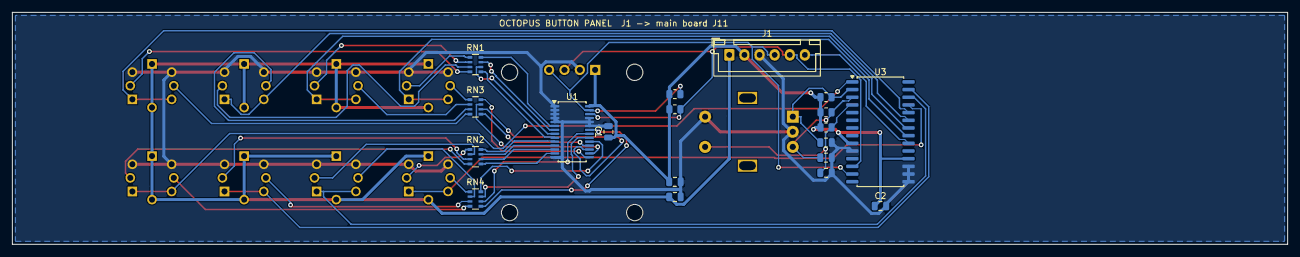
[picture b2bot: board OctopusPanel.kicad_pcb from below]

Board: 2 copper layers, 211.0 x 38.4 mm, 29 parts (19 on the bottom side), 49 nets.

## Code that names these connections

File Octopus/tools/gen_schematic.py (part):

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    for num, (lx, ly) in TEENSY_PINS.items():
        angle = 0 if lx < 0 else 180
        nm = TEENSY_PIN_NAMES[num]
        lines.append(f'\t\t\t(pin passive line (at {lx:g} {ly:g} {angle}) (length 2.54)')
        lines.append(f'\t\t\t\t(name "{nm}" (effects (font (size 1.27 1.27))))')
        lines.append(f'\t\t\t\t(number "{num}" (effects (font (size 1.27 1.27)))))')
    lines.append('\t\t)')
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
# DIN pin 4 -> 220R -> opto LED anode; DIN pin 5 -> LED cathode; 1N4148 reverse-parallel
# across the LED (cathode on the LED's anode)
for part, local, pin, net in ((J1, DIN_PINS, "4", "MIDI_IN_4"), (R1, R_PINS, "1", "MIDI_IN_4"),
                              (R1, R_PINS, "2", "OPTO_A"), (U2, OPTO_PINS, "2", "OPTO_A"),
                              (J1, DIN_PINS, "5", "OPTO_K"), (U2, OPTO_PINS, "3", "OPTO_K"),
                              (D1, D_PINS, "1", "OPTO_A"), (D1, D_PINS, "2", "OPTO_K")):
    pin_stub(part[pin], auto_dir(local[pin]), net)

# Output side runs at 3.3 V: the Teensy 4.1 is NOT 5 V tolerant, so the opto is fed
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# long way round, avoiding crossing straight through the Teensy body
wire_path([MIDI_RX, (125, MIDI_RX[1]), (125, U1["0"][1]), U1["0"]])

# Line n: 1-8 drive jack 1-8 TIP via U3 from Teensy pins 2-9; 9-16 drive jack 1-8 RING
# via U5 from pins 24-31. Within each driver, slot k (1..8) uses input I(9-k) / output
# O(9-k): both parts are counter-clockwise numbered, so on the PCB (Teensy above, ULN
# inputs facing it) this reversal is what lets the driver traces run straight.
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def uln_out_pin(k):
    return str(10 + k)         # O(9-k) is DIP pin 19-(9-k)

LINES = {}                     # line n -> (teensy pin, driver refdes, driver pins, slot k)
for k in range(1, 9):
    LINES[k] = (k + 1, "U3", U3, k)
    LINES[k + 8] = (k + 23, "U5", U5, k)
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# through two 74HCT14 inverters in series -- HCT inputs switch at TTL levels, so 3.3 V drives
# them while they run from 5 V -- to a standard 5 V MIDI source: pin 4 -> 220R -> +5V,
# pin 5 -> 220R -> buffer output. Pin 2 and the socket's screen are grounded (MIDI OUT/THRU).
label("MIDI_RX", MIDI_RX[0], MIDI_RX[1], 0)   # the opto output node also feeds the THRU buffer
gates = {1: ("MIDI_RX", "THRU_N"), 2: ("THRU_N", "THRU_TX")}   # (input, output) of the used gates
for u in range(1, 8):
    local = HC14_UNITS[u]
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J12 = place("Connector:DIN-5_180degree", "J12", "FM6725 MIDI THRU", 60, 310, DIN_PINS)
R3 = place("Device:R", "R3", "220", 110, 300, R_PINS)
R4 = place("Device:R", "R4", "220", 140, 300, R_PINS)
pin_stub(J12["4"], "L", "THRU_SRC")
pin_stub(J12["5"], "R", "THRU_SINK")
pin_stub(J12["2"], "U", pwr="GND")
no_connects.extend([J12["1"], J12["3"]])
pin_stub(R3["1"], "U", pwr="+5V")
pin_stub(R3["2"], "D", "THRU_SRC")
pin_stub(R4["1"], "U", "THRU_TX")
pin_stub(R4["2"], "D", "THRU_SINK")

# ------------------------------------------------------- button panel link
# 6-pin cable to the button board (panel/OctopusPanel); its I2C pull-ups live there.
for pin, net in (("18", "I2C_SDA"), ("19", "I2C_SCL"), ("22", "PANEL_INT")):
    px, py = U1[pin]
    end = (round(px - 5.08, 4), py)
    add_wire((px, py), end)
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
